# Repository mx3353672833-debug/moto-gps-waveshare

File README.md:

<p>
  
</p>

> **语言 / Language:** 中文 · [English](README.en.md)

# MOTO GPS · Waveshare Edition

[Glimpse 官网](https://maler.top/) · [2026-09-16 近期更新](docs/UPDATES_2026-09-16.md) · [Web 调试入口](https://maler.top/moto-gps/ride.html)

**想自己做一台微雪版？从 [购买、固件烧录与 iPhone 安装教程](docs/WAVESHARE_DIY_GUIDE.md)开始。**

[功能与使用说明书](docs/USER_MANUAL.md) · [真实导航网关配置](docs/GATEWAY_SETUP.md)

**用安卓手机？** 仓库已包含原生 [Android App](platforms/android/README.md)（Kotlin + Compose，与 iOS 共用导航核心和蓝牙协议，不依赖 Google Play 服务），可自行编译安装；真机配对与骑行仍在验证中。继续改进可参考 [用 AI 开发安卓版本](docs/ANDROID_AI_GUIDE.md)。

~~**欢迎一起共创 Glimpse。** 如果你基于这个项目做出了安卓 App，希望你愿意把源码也公开到 GitHub，让其他人能够学习、使用并一起维护。可以先在 [Issues](https://github.com/mx3353672833-debug/moto-gps-waveshare/issues) 聊想做的功能，再通过 Pull Request 贡献代码、修复或文档；请附上构建说明和已测试的机型。我们会保留贡献者署名，相关代码沿用项目现有许可。具体参与方式见 [安卓共创邀请](docs/ANDROID_AI_GUIDE.md#一起开发安卓版本)。~~

当前提供源码自行编译安装；尚无仓库发布的预编译固件、App Store / TestFlight 下载入口。
**iOS 0.3.0（5）已加入发布准备改动，尚未通过 TestFlight 分发。**
教程包含设备选型、原厂备份、Xcode 个人签名、配对、演示与常见问题。

**作者：Maler X · 署名 / 非商业使用 · 实验性样机**

一块装在车把上的圆屏，一个放在包里的 iPhone。手机负责定位、搜索与路线计算，
圆屏通过蓝牙显示简洁导航、速度、相对航向，并遥控 Apple Music。

项目基于 **Waveshare ESP32-S3-Touch-AMOLED-1.75C**，
包含圆屏固件、iOS App、路线网关和网页调试工具。

仓库同时收录自研电路板、V3 外壳、加工审阅资料和完整产品技术方案。
当前运行版本仍是微雪成品板 + iPhone；自研部分按历史工程候选归档，具体版本见下方资料入口。
B1 手机配套主板与 V3 外壳目前暂停推进，现阶段集中完善微雪版本。
首图为产品外观效果图，实物与加工尺寸请以对应版本的工程文件为准。

出发前在手机上搜索目的地、比较路线；开始导航后，车把上的圆屏显示眼前路口、
转向动作和距离。地图围绕固定的车头箭头移动，灰色道路和建筑提供周围环境参照。
滑动屏幕，还可以查看速度、航向，或操作 Apple Music。

[功能详解](#功能详解) · [使用流程](#使用流程) · [硬件与开发环境](#硬件与开发环境) ·
[安装与配置](#安装与配置) · [开发与测试](#开发与测试) · [使用许可](#使用许可与署名)

[产品参数](docs/PRODUCT_SPECIFICATIONS.md) · [电路板与外壳](hardware/README.md) ·
[技术方案 PDF / DOCX](docs/technical-proposal/README.md) · [资料总目录](docs/PROJECT_DOCUMENTATION.md)

## 电路板、外壳与产品资料

| 资料 | 包含内容 | 入口 |
| --- | --- | --- |
| 产品说明与技术参数 | 微雪样机与自研 A1 对照、显示与通信、结构尺寸、数据来源与验证状态 | [产品参数](docs/PRODUCT_SPECIFICATIONS.md) |
| H0175 EVT A1 自研主板 | KiCad 原理图与四层 PCB、项目符号封装库、BOM/CPL、Gerber/钻孔、装配图、ERC/DRC 和 SHA-256 | [A1 完整审阅包](hardware/manufacturing/engineering-candidates/rev-a1-h0175-evt1-20260903/README_DO_NOT_ORDER.md) |
| Rev A0 R4 主板 | A1 之前的路由基线与完整电气审阅资料，保留早期修订供比较 | [R4 审阅包](hardware/manufacturing/engineering-candidates/rev-a0-20260903-r4/README_DO_NOT_ORDER.md) |
| V3 自研外壳 | 参数化 CAD、前框/后壳/卡口 STEP 与 STL、装配模型、二维图、结构规格及外观渲染 | [V3 文件说明](hardware/mechanical/README.md) |
| 产品技术方案 | H0175 EVT A1 与 Rev A0 两版 Markdown、PDF、可编辑 Word，附系统架构与产品配图 | [阅读与下载](docs/technical-proposal/README.md) |
| 审查与生成工具 | 器件封装审计、电气检查、候选包导出脚本及硬件发布检查测试 | [硬件工具](scripts/hardware/README.md) |

自研 A1 使用 Ø52 mm 四层板，历史方案集成 ESP32-S3、LC76G、IMU、磁力计和
充电电源；V3 外壳名义主体 Ø61 × 16 mm，含卡口约 19 mm。这些参数属于自研
设计资料，与当前微雪板的尺寸和器件配置分开列出。A1、R4 均为工程审阅版本，
保留原有 `DO NOT ORDER` 标识；上传资料不代表恢复打样或已完成生产验收。

## 目前有什么

| 模块 | 功能 |
| --- | --- |
| 圆屏导航 | 白色路线、下一动作图标与距离；真实道路限速和红绿灯倒计时尚未接通 |
| iPhone | 原生导航栏与分组列表、浅深色与大字体、位置偏置搜索、搜索历史、路线预览与候选选择 |
| 导航逻辑 | 共享 C++ 核心，路线进度、偏航检测、联网重算与周期路线/路况刷新 |
| 灰色道路 / 建筑 | 默认在线加载周边 OSM / Protomaps 底图；支持城市、区县与沿途下载，保留内置济南地图兜底 |
| 马表 / 航向 | 手机定位提供速度与行驶方向，板载 QMI8658 辅助相对转向 |
| 音乐 | Apple Music 上一首、播放/暂停、下一首 |
| 动效 / 触摸 | 黑白 Logo 淡入淡出、连接状态过渡、滑动切页、指示点自动隐藏、PWR 长按关机 |
| 演示 | 济南大数据产业基地 D 栋附近 → 浪潮总部附近；在线请求与 OSM 离线回退明确区分 |

## 功能详解

### 圆屏导航：把下一个路口看清楚

导航页以黑色为底，白色路线和转向提示是画面的重点。466×466 的圆形显示区域中，
每种元素都有明确含义：

| 画面元素 | 表达的信息 |
| --- | --- |
| 固定车头箭头 | 当前行进位置的视觉锚点，指向屏幕前方 |
| 白色粗线 | 当前导航路线在附近的走向 |
| 灰色细线 | 周围道路的实际几何形状，帮助辨认路口、支路和道路关系 |
| 灰色建筑块 | OSM 中收录的建筑轮廓，提供街区和园区参照 |
| 左下动作图标 | 下一个路口的直行、左转、右转、掉头等动作 |
| 动作旁的大号距离 | 距离这个动作还有多远，按距离切换 `m` / `km` |
| 限速牌 | 已有显示结构，但真实道路限速尚未接通；缺少数据时隐藏 |
| 底部圆弧 | 路线完成进度，颜色随当前路况状态变化 |

例如屏幕显示右转箭头和 `300 m`，意思就是沿当前路线行驶约 300 米后右转。
接近路口时，距离逐渐减少；通过路口后，图标和数字更新为下一项指引。

行驶和转弯时，路线、周边道路和建筑使用同一组位置、航向和缩放参数。
车头箭头保持固定，地图在它下面平移、旋转，便于连续观察前方道路。
圆屏聚焦当前路段，出发前的全程路线由 iPhone 的预览地图展示。

### 地点搜索与路线选择

iPhone App 使用高德地点搜索与普通驾车路线服务。搜索时会带上手机当前位置，
优先呈现附近、相关度较高的地点。在济南输入“奥体中心”这样的关键词即可开始检索，
也可以输入带城市名的外地地点。
当前是普通驾车路线，不保证避开摩托车禁限行道路。

搜索与选路流程包括：

- 输入至少两个字开始搜索，连续输入时合并请求，按最新关键词更新结果。
- 搜索结果显示地点名称、地址或所在区域；有当前位置时可展示距离。
- 选择地点后保存到最近地点列表，按使用顺序保留 **8 条**，重启 App 后继续保留。
- 点击最近地点可重新规划前往该处的路线，也可以一键清空历史。
- 规划前刷新起点位置，再向网关请求候选路线。
- 按高德实际返回结果提供 **最多 3 条路线**，以推荐路线、备选路线展示。

路线确认页会显示起点、终点和整条路线。选中的路线高亮，其余候选以浅色显示。
下方卡片列出各条路线的距离、预计时间和分段路况摘要，例如“路况顺畅”“部分路段缓行”。
点击卡片切换方案，确认后再点击“开始导航”。

开始时会将选中的路线交给导航核心；如果预览后起点已经明显移动，程序会从当前位置
重新规划。路线确认与真机显示的一致性是当前持续回归测试的项目之一。

### 行驶中的导航更新

导航核心根据连续定位更新路线进度、下一动作距离、剩余路程和预计剩余时间。
手机导航页同时显示目的地、圆屏连接状态、定位状态与当前路况。

偏航判断结合偏离距离与连续定位确认。满足条件后，App 发起重新规划，
取得新路线后将指引同步给圆屏。路况通过周期请求刷新；核心默认配置约每 60 秒
发起一次更新，实际请求节奏还受网络状态、重试和服务配额影响。
当前路线仍以白线显示，按路段着色及未知、过期路况的呈现仍在完善。
红绿灯倒计时和可信的当前道路限速数据尚未接通。

定位质量、请求编号、路线版本都参与状态更新。手机保留当前导航状态，
圆屏重新完成连接和协议握手后，程序会尝试补发最新路线与显示数据。
后台连接和跨城路线的验证进展集中记录在[开发进度](#开发进度)。

### 在线周边地图与离线下载

背景小地图使用 OpenStreetMap / Protomaps 道路和建筑数据。配置可用网关后，
导航默认按当前位置在线加载周边底图，保存已访问区域；网络不可用时复用本地数据。
底图已经不限于随包的济南数据，但能否下载及当地道路、建筑完整程度取决于数据源与网络。

在 iPhone 首页进入「地图与离线下载」：

- 「下载城市地图」可搜索城市或区县，预览范围后下载；范围较大时建议先选区县。
- 选好路线后，可「下载这条路线周边」，保存沿途约一公里范围的底图。
- 下载可以暂停、继续和删除；自动缓存最多 128 MB，手动下载最多 512 MB，共用瓦片只保存一份。
- 离线底图不包含实时路况；搜索地点、规划新路线和联网重算仍需要网络。

原有济南 SQLite 地图库仍随 App 提供，作为覆盖区域内的本地兜底：

| 当前内置数据包 | 数量 |
| --- | ---: |
| 文件体积 | 9.73 MiB |
| 道路折线 | 47,468 条 |
| 道路节点 | 266,985 个 |
| 建筑轮廓 | 26,702 个 |
| 建筑节点 | 148,140 个 |

导航时，手机从在线瓦片、已保存地图或可用的济南兜底数据中筛选当前位置周围约 500 米
的道路和建筑，再通过 BLE 发给圆屏。查询窗口随位置滚动，圆屏不保存整座城市地图。

目前单个显示窗口最多容纳 24 条背景道路、192 个道路点，以及 16 个建筑、128 个建筑点。
这种分工让手机保存完整区域数据，圆屏负责绘制当前视野。地图密度取决于当地 OSM
收录情况、要素筛选策略和窗口容量；建筑覆盖较完整的区域会有更丰富的街区细节。

路线规划与路况由在线高德服务提供，圆屏灰色环境图层来自 OSM / Protomaps，
手机全程预览底图由 Apple 地图提供。它们是不同数据层，离线下载不等于离线导航。
长期部署需准备稳定、获准使用的数据源，保留 OSM 署名与许可入口。
新流程见[近期更新](docs/UPDATES_2026-09-16.md)，原有数据库格式和重建工具见
[离线地图说明](shared/offline_map/README.md)。

### 马表与航向页

马表页以大号数字显示当前速度，单位为 `km/h`，外圈刻度和圆弧随速度变化。
页面围绕实时速度设计，适合在圆屏上快速读取。

航向页显示角度、方位字母、旋转刻度和当前速度。手机定位提供行驶方向，
圆屏上的 QMI8658 六轴传感器提供短时角速度，用于补偿转动过程中的显示变化。

手机放在包里时，行驶方向取自位置运动产生的 `CLLocation.course`；
圆屏的相对转角取自设备自身陀螺仪。低速或静止时冻结不可靠的航向变化并抑制残余速度，
恢复行驶后再由定位航向逐渐校正。静止绝对北向属于后续磁力计扩展的范围。

### Apple Music 控制

音乐页通过 iPhone 的系统音乐播放器控制 Apple Music，显示音乐来源、曲目标题、
歌手和播放状态。圆屏提供上一首、播放/暂停、下一首三个操作按钮。

首次使用时，在 iPhone 上授权媒体资料库访问，并在 Apple Music 中准备好播放队列。
触摸圆屏按钮后，命令经 BLE 发送到手机；播放器处理动作后，最新曲目与状态再回传圆屏。
手机授权状态和播放器状态决定音乐功能的可用情况。

声音继续沿用 iPhone 当前的音频输出，例如头盔蓝牙耳机。圆屏承担显示与遥控，
适合与手机现有的音乐播放方式搭配使用。

### 开机、连接与触摸交互

上电后先显示黑白 `MOTO GPS` Logo，经过淡入、停留和淡出进入连接界面。
面板在纯黑首帧准备好后点亮，减少启动闪白。

```text
开机 Logo → 准备连接 / 连接中 → 绿色连接成功 → 准备出发 → 导航画面
```

准备连接时显示连接图形和动画；协议握手完成后，绿色成功状态停留约 0.9 秒，
再进入准备出发页，提示到手机选择目的地。开始规划与取得路线时，页面继续随状态切换。

- 左右滑动切换导航、马表、航向、音乐页面；音乐页按手机能力开放。
- 底部指示点用于识别当前页面，停留五秒后自动隐藏。
- 触摸或换页后，指示点重新出现。
- 侧面 PWR 按住约三秒，显示关机画面并向 AXP2101 请求关机；USB 供电场景还有深睡处理。

### 演示导航

App 提供“演示导航”入口，使用以下公共地点作为固定演示场景：

**济南大数据产业基地 D 栋附近 → 浪潮集团总部附近。**

联网演示优先请求当次高德路线，再沿返回的路线几何连续生成模拟位置。
离线回退使用随仓库提供的 OSM 路线，经过园区车道、新泺大街、崇华路和浪潮路，
全长约 1.49 公里。演示位置同样经过导航核心、BLE 协议和圆屏 UI。

坐在桌前即可观察动作图标与距离的对应关系、地图滚动、转弯旋转、周边灰路与建筑，
也能检查连接状态切换和页面排版。Web 工具提供同源界面的浏览器预览。
演示数据的道路来源、生成方式和 OSM 署名见[演示夹具说明](shared/demo_fixture/README.md)。

## 使用流程

完成首次安装和配置后，一次导航按下面的顺序操作：

1. 给圆屏上电，在 iPhone 上打开 MOTO GPS。
2. 查看连接状态；首次配对时按 iOS 提示完成蓝牙配对和权限授权。
3. 输入目的地，或者从最近地点中选择一个终点。
4. 在全程地图中查看路线，比较候选卡片的距离、用时与路况。
5. 选择路线并点击“开始导航”，手机开始更新位置，圆屏显示当前路段和下一动作。
6. 停车时可滑动查看马表、航向和音乐页面，按需切歌。
7. 到达后查看到达状态，在手机上结束导航；收车时长按圆屏 PWR 关机。

iPhone 提供网络和定位，圆屏通过 BLE 连接手机。当前后台连接可靠性仍在验证中，
请先在安全静止环境完成锁屏、恢复连接和状态同步测试。
调试及操作请停车后进行，行驶时请结合成熟导航软件核对路线。

## 硬件与开发环境

### 终端硬件

| 项目 | 当前适配 |
| --- | --- |
| 开发板 | Waveshare ESP32-S3-Touch-AMOLED-1.75C |
| 主控 | ESP32-S3 |
| 存储 | 32 MB Flash、8 MB PSRAM |
| 显示 | 1.75 英寸圆形 AMOLED，466×466 |
| 显示驱动 | CO5300，QSPI，RGB565 |
| 触摸 | CST9217 电容触摸 |
| 运动传感器 | QMI8658 六轴 IMU |
| 电源管理 | AXP2101，USB-C / 配套锂电池 |
| 手机连接 | BLE，自定义导航 GATT 服务 |

准备一条支持数据传输的 USB-C 线。使用电池时，按微雪对 **1.75C** 的规格、
插头和极性要求选择。刷写前请核对完整板型；板级连接与固件步骤见
[ESP32 说明](platforms/esp32/README.md)。

### 软件工具

| 用途 | 环境 |
| --- | --- |
| iPhone App | iOS 17+；Mac、Xcode 16+ / Swift 6 工具链、XcodeGen |
| 圆屏固件 | ESP-IDF **5.5.5**，Waveshare BSP **3.0.0** |
| 共享 UI | LVGL **9.5.0 对应固定提交** |
| 路线网关 | Node.js 20+；建议 Node.js 24+ 运行本文配置示例 |
| C++ 测试 | CMake、支持 C++17 的编译器 |
| Web 预览 | Emscripten、CMake、HTTP 静态服务器 |
| 地图重建 | Node.js 24+、osmium-tool、jq |

真实导航需要配置自己的高德 Key、HTTPS 网关和 Apple 开发者签名。

## 安装与配置

### 1. 获取源码

```sh
git clone --recurse-submodules https://github.com/mx3353672833-debug/moto-gps-waveshare.git
cd moto-gps-waveshare
```

上述命令会同时获取固定版本的 LVGL。使用 GitHub 的 Download ZIP 时，
还需将 LVGL 提交 `85aa60d18b3d5e5588d7b247abf90198f07c8a63` 的源码放入 `third_party/lvgl/`。

下面的命令均以仓库根目录为起点。

### 2. 配置路线网关

也可以选择新增的 [Cloudflare Workers + R2 部署](backend/cloudflare/README.md)，无需维护 Node 服务器。下面仍是原有服务器方案。

网关将 App 的搜索和路线请求转换为高德 Web 服务请求，再返回统一格式的导航数据。
高德 Key 保存在服务端环境变量中。

先运行后端自动测试，再创建自己的配置文件：

```sh
npm ci --prefix backend
npm --prefix backend test
cp backend/.env.example backend/.env
```

编辑 `backend/.env`：

| 配置项 | 填写内容 |
| --- | --- |
| `MOTO_PROVIDER` | 真实导航填写 `amap`；本地协议测试用 `fixture`；待配置服务用 `disabled` |
| `AMAP_WEB_SERVICE_KEY` | 自己申请的高德 Web 服务 Key |
| `PORT` | 后端监听端口，默认 `8787` |
| `WEB_ORIGIN` | 使用 Web 工具时填写网页的实际 Origin |
| `MOTO_MAP_PMTILES_URL` | `auto` 选择兼容的 Protomaps 构建；也可指定自己的 HTTPS PMTiles 地址，`disabled` 关闭在线底图 |
| `MOTO_MAP_CACHE_DIR` | 地图缓存目录，默认 `.cache/map-tiles` |
| `MOTO_MAP_CACHE_MAX_BYTES` | 服务端缓存字节上限，默认 `1073741824` |

用 Node.js 24+ 显式加载配置并启动：

```sh
node --env-file=backend/.env backend/src/server.js
```

服务默认监听 `127.0.0.1:8787`。部署时，用自己的 HTTPS 反向代理把
`/moto-gps/api/` 转发到这个服务，供手机访问。
检查 `/healthz` 中的 `provider` 为 `amap`、`ready_for_live_navigation` 为 `true`，
再完成一次真实地点搜索与路线请求，确认账号权限、配额和网络。

对公网部署时，请配置访问控制、TLS、配额限制和日志脱敏。
完整 API 与部署说明见[路线网关文档](backend/README.md)。

### 3. 构建并安装 iPhone App

也可以直接下载 IPA，在 App 中填写网关地址，无需自己用 Mac 编译：[IPA 安装说明](docs/IOS_SIDELOAD.md)。

编辑 `platforms/ios/project.yml`，设置：

- `MOTOGPSGatewayBaseURL`：自己的 HTTPS 网关地址，例如 `https://YOUR-DOMAIN/moto-gps/api/`。
- `PRODUCT_BUNDLE_IDENTIFIER`：自己可用的唯一标识；App 与两个测试目标分别设置。
- `DEVELOPMENT_TEAM`：自己的签名团队，也可以在 Xcode 中选择。

App 默认网关为示例地址 `https://example.invalid/moto-gps/api/`，使用前替换成自己的服务。
配置来源是 `project.yml`，XcodeGen 会据此更新工程与 `Info.plist`。

```sh
(cd platforms/ios && xcodegen generate)
open platforms/ios/MotoGPS.xcodeproj
```

连接并信任自己的 iPhone，按 Xcode 提示启用开发者模式，选择 MotoGPS scheme、
自己的设备和签名团队，再点击 Run 安装。
首次运行按提示允许定位、精确位置、蓝牙及所需媒体权限。
详细步骤和签名说明见[iOS 文档](platforms/ios/README.md)。

### 4. 构建并刷入圆屏

安装、激活 ESP-IDF 5.5.5 环境后执行：

```sh
idf.py -C platforms/esp32 set-target esp32s3
idf.py -C platforms/esp32 build
```

构建会获取固定依赖，在 `platforms/esp32/build/` 生成应用、bootloader 和分区表。
首次刷写前，按[固件文档的备份步骤](platforms/esp32/README.md#备份和刷写)
核对型号、Flash 容量和安全状态，保存原厂完整备份。

确认备份完成并接受替换原厂应用后，将 `PORT` 换成实际 USB 串口：

```sh
idf.py -C platforms/esp32 -p PORT flash monitor
```

设备启动后以 `MOTO GPS` 广播。打开 iPhone App 完成配对与握手，
圆屏进入准备出发页后，即可按照上面的使用流程选择路线。

### 5. 在浏览器预览界面

安装并激活 Emscripten 后，构建共享 LVGL WebAssembly 运行时：

```sh
./scripts/build_web.sh
python3 -m http.server 4173 --directory .
```

浏览器打开：

```text
http://127.0.0.1:4173/platforms/web/shell/index.html?demo=1
```

也可以分别预览连接状态，把查询参数改为 `?deviceState=connecting`、
`?deviceState=success`、`?deviceState=ready` 或 `?deviceState=planning`。
这些状态使用共享 LVGL 界面渲染，适合开发时检查动画和排版。

查看和调试界面可用 [Web 调试工具](platforms/web/shell/README.md)，使用时保持网页前台亮屏。
线上调试入口是 [/moto-gps/ride.html](https://maler.top/moto-gps/ride.html)；
[Glimpse 官网](https://maler.top/) 位于域名首页，网站本身不开源。
手机后台定位和 BLE 连接由 iOS App 负责，当前验证进度见[已知问题](docs/KNOWN_ISSUES.md)。

## 实现方式

iPhone 负责位置、完整路线、地图下载与缓存，ESP32 负责接收显示状态、处理本机运动输入、
绘制圆屏和回传触摸命令。后端负责高德服务调用、Protomaps 数据读取、格式转换与缓存。

```text
高德 Web 服务 ───────┐
OSM / Protomaps ─────┴→ HTTPS 网关与缓存 ←→ iPhone App
                                      │
                Core Location + 共享导航核心 + 在线 / 离线地图查询
                                      │ BLE
                                      ▼
                   ESP32 接收状态 + QMI8658 相对转向
                                      │
                           NavPresenter → LVGL → 圆屏

圆屏触摸 / 音乐操作 ─────── BLE ───────→ iPhone
```

### 共享导航与界面

路线进度、偏航状态和显示数据结构放在共享 C++ 模块中。iOS 通过 Objective-C++ 桥接调用
导航核心；Web 和 ESP32 共同编译 `NavPresenter` 与 LVGL UI。
调整圆屏布局、动作图标或地图绘制时，可以先用 Web 观察，再在实机验证。

完整路线保存在手机端，圆屏接收当前视野所需的路线几何与周边环境窗口。
请求位置使用 WGS84，导航几何统一为 GCJ-02；地图预览按平台坐标要求进行转换。
相关约定见[架构说明](docs/ARCHITECTURE.md)和[路线协议](shared/protocol/README.md)。

### BLE 数据与连接

设备以 GATT peripheral 工作，iPhone 作为 central 连接。
协议包含连接状态、心跳、导航快照、路线几何、路况、道路/建筑窗口、媒体状态和设备命令。

传输层实现分片重组、CRC 校验、消息序号、会话隔离、控制命令 ACK 与超时重试。
手机到圆屏的导航快照最高按 5 Hz 调度，位置和转向动画由终端进一步插值。
配对采用加密 BLE 连接与 bonding；连接恢复仍在持续测试。
心跳只发送当前应用会话的已用时间，不发送手机系统启动时长。
GATT UUID、字节格式与黄金测试数据见[BLE 协议](shared/protocol/ble-navigation-v1.md)。

### 显示与流畅度

固件使用 PSRAM 绘图缓冲与直接 DMA，让 LVGL 绘制和 QSPI 传输衔接。
CO5300 的 TE 信号用于帧首同步，地图、插值和渲染任务按 25 ms 的目标节拍协调。
实际帧率、快速转向时的撕裂感和持续运行功耗，仍以实机测量与观察为准。

## 源码结构

```text
platforms/ios       iPhone 定位、路线预览、BLE、Apple Music、在线 / 离线地图
backend            Node.js 高德服务与 Protomaps 地图网关、缓存（Key 只在服务端）
platforms/esp32     Waveshare 板级适配、BLE、QMI8658、显示与电源
shared             共享导航核心、协议、LVGL UI、OSM 演示及地图数据
platforms/web      LVGL / Wasm 调试外壳
website            Glimpse 官网源码与部署说明
tests              C++ 原生测试
scripts            Web 构建、字体与 OSM 地图工具
```

详见 [架构与数据边界](docs/ARCHITECTURE.md)、[测试方式](docs/TESTING.md)、
[已知问题](docs/KNOWN_ISSUES.md)、[第三方许可证](THIRD_PARTY_NOTICES.md)。

## 开发与测试

### 运行自动测试

在仓库根目录执行：

```sh
cmake -S . -B build/native -DMOTO_BUILD_WEB=OFF -DMOTO_BUILD_TESTS=ON
cmake --build build/native --parallel 4
ctest --test-dir build/native --output-on-failure

npm ci --prefix backend
npm --prefix backend test
swift test --package-path platforms/ios

node scripts/generate_jinan_demo_fixture.mjs --check
node scripts/offline_map/validate_jinan_sqlite.mjs
```

2026-09-16 本轮通过 9 组 C++ 原生测试、60 项后端测试、12 项 Swift 核心测试，
并有 13 项 BLE 策略测试通过记录；演示夹具一致性与地图数据库完整性检查通过。
这些结果验证代码和数据路径，不代表真实道路、长时间锁屏或续航验收完成。
本轮范围见[近期更新](docs/UPDATES_2026-09-16.md)；首次公开快照的历史结果保留在
[发布检查记录](docs/RELEASE_CHECKS.md)，提交后的检查结果见
[GitHub Actions](https://github.com/mx3353672833-debug/moto-gps-waveshare/actions/workflows/checks.yml)。

### 从哪里开始修改

| 想调整的内容 | 主要入口 |
| --- | --- |
| 圆屏布局、颜色、图标、状态动画 | `shared/nav_ui/src/moto_nav_ui.cpp` |
| 地图投影与显示数据转换 | `shared/nav_presenter/src/moto_nav_presenter.cpp` |
| 偏航、到达、定位有效期和路况刷新默认配置 | `shared/nav_core/nav_core.hpp` 中的 `NavCoreConfig` |
| 手机搜索、历史记录、路线确认流程 | `platforms/ios/App/AppModel.swift`、`ContentView.swift` |
| 全程路线地图与候选展示 | `platforms/ios/App/RouteOverviewMap.swift` |
| BLE 握手、发送调度与恢复连接 | iOS 的 `ESP32BLECentral.swift` 与 ESP32 的 `ble_nav_transport_nimble.cpp` |
| 当前窗口道路与建筑筛选 | `platforms/ios/App/Adapters/OfflineMap/` |
| Apple Music 遥控 | `platforms/ios/App/Adapters/Media/AppleMusicRemoteController.swift` |
| CO5300 显示、TE 同步与电源 | `platforms/esp32/main/board_port_waveshare_1_75c.cpp` |
| 地图数据重建 | `scripts/offline_map/` |

修改协议时请同步更新两端实现和 golden fixture；修改地图时保留 OSM 来源、许可和署名。
贡献流程见[CONTRIBUTING](CONTRIBUTING.md)。

## 开发进度

当前版本处于实机验证阶段，接下来重点回归：

- iPhone 锁屏、切换网络和离开原环境后的 BLE 连接恢复。
- 跨城候选路线生成，以及手机选中路线与圆屏显示的一致性。
- 在线与离线地图切换、下载中断恢复，以及路况分段显示和过期状态。
- 快速转向时的刷新连续性、TE 同步表现和持续帧率。
- USB、电池及组合供电下的关机、唤醒、续航和温升。

功能说明描述的是当前源码实现；最新发布与验证边界见[近期更新](docs/UPDATES_2026-09-16.md)，
历史问题见[已知问题](docs/KNOWN_ISSUES.md)。提交问题时请附上板型、固件版本、iOS 版本、
复现步骤与脱敏日志，便于区分定位、网关、协议和显示环节。

## 使用许可与署名

项目原创代码和设计素材使用 **[PolyForm Noncommercial 1.0.0](LICENSE.md)**。
允许许可范围内的个人学习、研究、非商业使用和修改；分发源码、修改版、固件或 App
时必须携带许可证及 [NOTICE](NOTICE) 中的作者声明，注明 **Maler X** 和本仓库来源。
App 待机界面和 Web 状态页也提供可见署名入口。

**仅限非商业使用。** 销售预装设备、收费分发固件、用于商业产品或收费服务等用途，
须另行联系作者取得商业授权。具体授权范围以 LICENSE.md 正文为准。

授权类型为 **source-available（公开源码、非商业授权）**。
第三方库、字体和 OSM 数据分别遵循原许可证；地图服务须按服务商协议使用。

© 2026 Maler X · 地图数据 © OpenStreetMap contributors（ODbL 1.0）。

## Star History

<a href="https://star-history.com/#mx3353672833-debug/moto-gps-waveshare&Date">
 <picture>
   <source media="(prefers-color-scheme: dark)" srcset="https://api.star-history.com/svg?repos=mx3353672833-debug/moto-gps-waveshare&type=Date&theme=dark" />
   <source media="(prefers-color-scheme: light)" srcset="https://api.star-history.com/svg?repos=mx3353672833-debug/moto-gps-waveshare&type=Date" />
   
 </picture>
</a>

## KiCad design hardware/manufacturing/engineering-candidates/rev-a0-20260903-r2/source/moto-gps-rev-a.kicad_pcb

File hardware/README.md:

> **语言 / Language:** 中文 · [English](README.en.md)

# MOTO GPS 自研电路板与外壳

这里保存已完成的主板设计、制造审阅文件、外壳模型和核验记录。当前软件样机使用微雪成品板；
自研主板与外壳处于归档/暂停状态。完整资料公开供阅读、研究和工程评审。

## 从哪里开始

| 目标 | 推荐文件 | 说明 |
| --- | --- | --- |
| 查看产品参数 | [参数对照](../docs/PRODUCT_SPECIFICATIONS.md) | 微雪样机与自研 A1 分开列出 |
| 打开最新自研 PCB | [A1 KiCad 工程](manufacturing/engineering-candidates/rev-a1-h0175-evt1-20260903/source/moto-gps-rev-a1.kicad_pro) | 下载整个 source 目录，保留符号与封装库 |
| 阅读 A1 电气状态 | [A1 状态单](rev_a/H0175_EVT_A1_STATUS.md) | 器件、接口、ERC/DRC 与待验证项 |
| 查看 BOM、CPL 和装配图 | [A1 documents](manufacturing/engineering-candidates/rev-a1-h0175-evt1-20260903/documents/) | 原理图 PDF、装配 PDF、器件清单与坐标 |
| 查看 Gerber / 钻孔 | [A1 审阅制造文件](manufacturing/engineering-candidates/rev-a1-h0175-evt1-20260903/review_gerbers_DO_NOT_ORDER/) | 保留工程审阅标记，尚未生产放行 |
| 对照前一版 PCB | [Rev A0 R4](manufacturing/engineering-candidates/rev-a0-20260903-r4/) | A1 的冻结路由基线 |
| 编辑/打印外壳原型 | [V3 STEP 与 STL](mechanical/generated/v3/) | 含前框、后壳、佳明卡口与装配模型 |
| 核对机械尺寸 | [V3 机械规格](mechanical/V3_MECHANICAL_SPEC.md)、[二维图](mechanical/drawings/) | 主体 Ø61 × 16 mm，含卡口约 19 mm，均为设计值 |
| 阅读完整方案 | [技术方案 PDF / Word](../docs/technical-proposal/README.md) | A1 与 A0 两版完整资料 |

A1 与 R4 的完整候选包都包含 `SHA256SUMS`，可在各候选包目录运行
`shasum -a 256 -c SHA256SUMS` 校验。封装、线路和规则检查记录随包提供。
优先使用这些完整候选包；下面保留的 `pcb/` 目录属于更早期的板框研究。

## 早期目录与设计记录

本目录承载 MOTO GPS 自研一体主板、制造文件和外壳 CAD。设计基线见 [自研一体硬件与外壳执行方案](../docs/CUSTOM_HARDWARE_PLAN.md)。

计划结构：

```text
hardware/
  pcb/
    moto-gps-rev-a.kicad_pro
    moto-gps-rev-a.kicad_sch
    moto-gps-rev-a.kicad_pcb
  libraries/       经复核的自建符号、封装与 3D 模型
  mechanical/      参数化外壳、STEP、STL 与 2D 加工图
  manufacturing/   Gerber、钻孔、BOM、CPL 和装配说明
  validation/      上电、RF、GNSS、罗盘、功耗和环境测试记录
```

在屏幕 FPC、电池、GNSS 天线和车把卡口四项冻结前，`manufacturing/` 中的任何文件都只能标为草案，不能直接批量下单。

CAD 工具链为 KiCad 10.0.6。`pcb/` 下的早期文件是 52 mm 圆板机械包络和空白原理图骨架。
后续 `rev_a/` 与制造候选包已经包含真实布线和完整电气设计；两类文件的零违规报告含义不同，
查看时请同时核对版本和工程内容。

已冻结/待冻结的关键接口：

- [屏幕与触摸 FPC 接口](pcb/DISPLAY_INTERFACE.md)：电气映射已整理，连接器接触面、Pin 1 与 FPC 厚度仍须用原装屏实物确认。
- [LC76G 与 GNSS RF 接口](pcb/GNSS_INTERFACE.md)：裸模组、低噪声供电、UART/PPS、U.FL 有源天线基线和塑料 RF 窗约束。
- [电源架构冻结条件](pcb/POWER_DECISION.md)：主方案已改为 BQ25628E + TPS63070 + TUSB320LAI，完整主板前须先通过独立电源测试券。
- [Rev A GPIO 预算](pcb/REV_A_PIN_BUDGET.md)。
- [Rev A0 参数化外壳](mechanical/README.md)：铝前框、塑料后壳、独立 RF 舱和可替换车把卡口概念件。

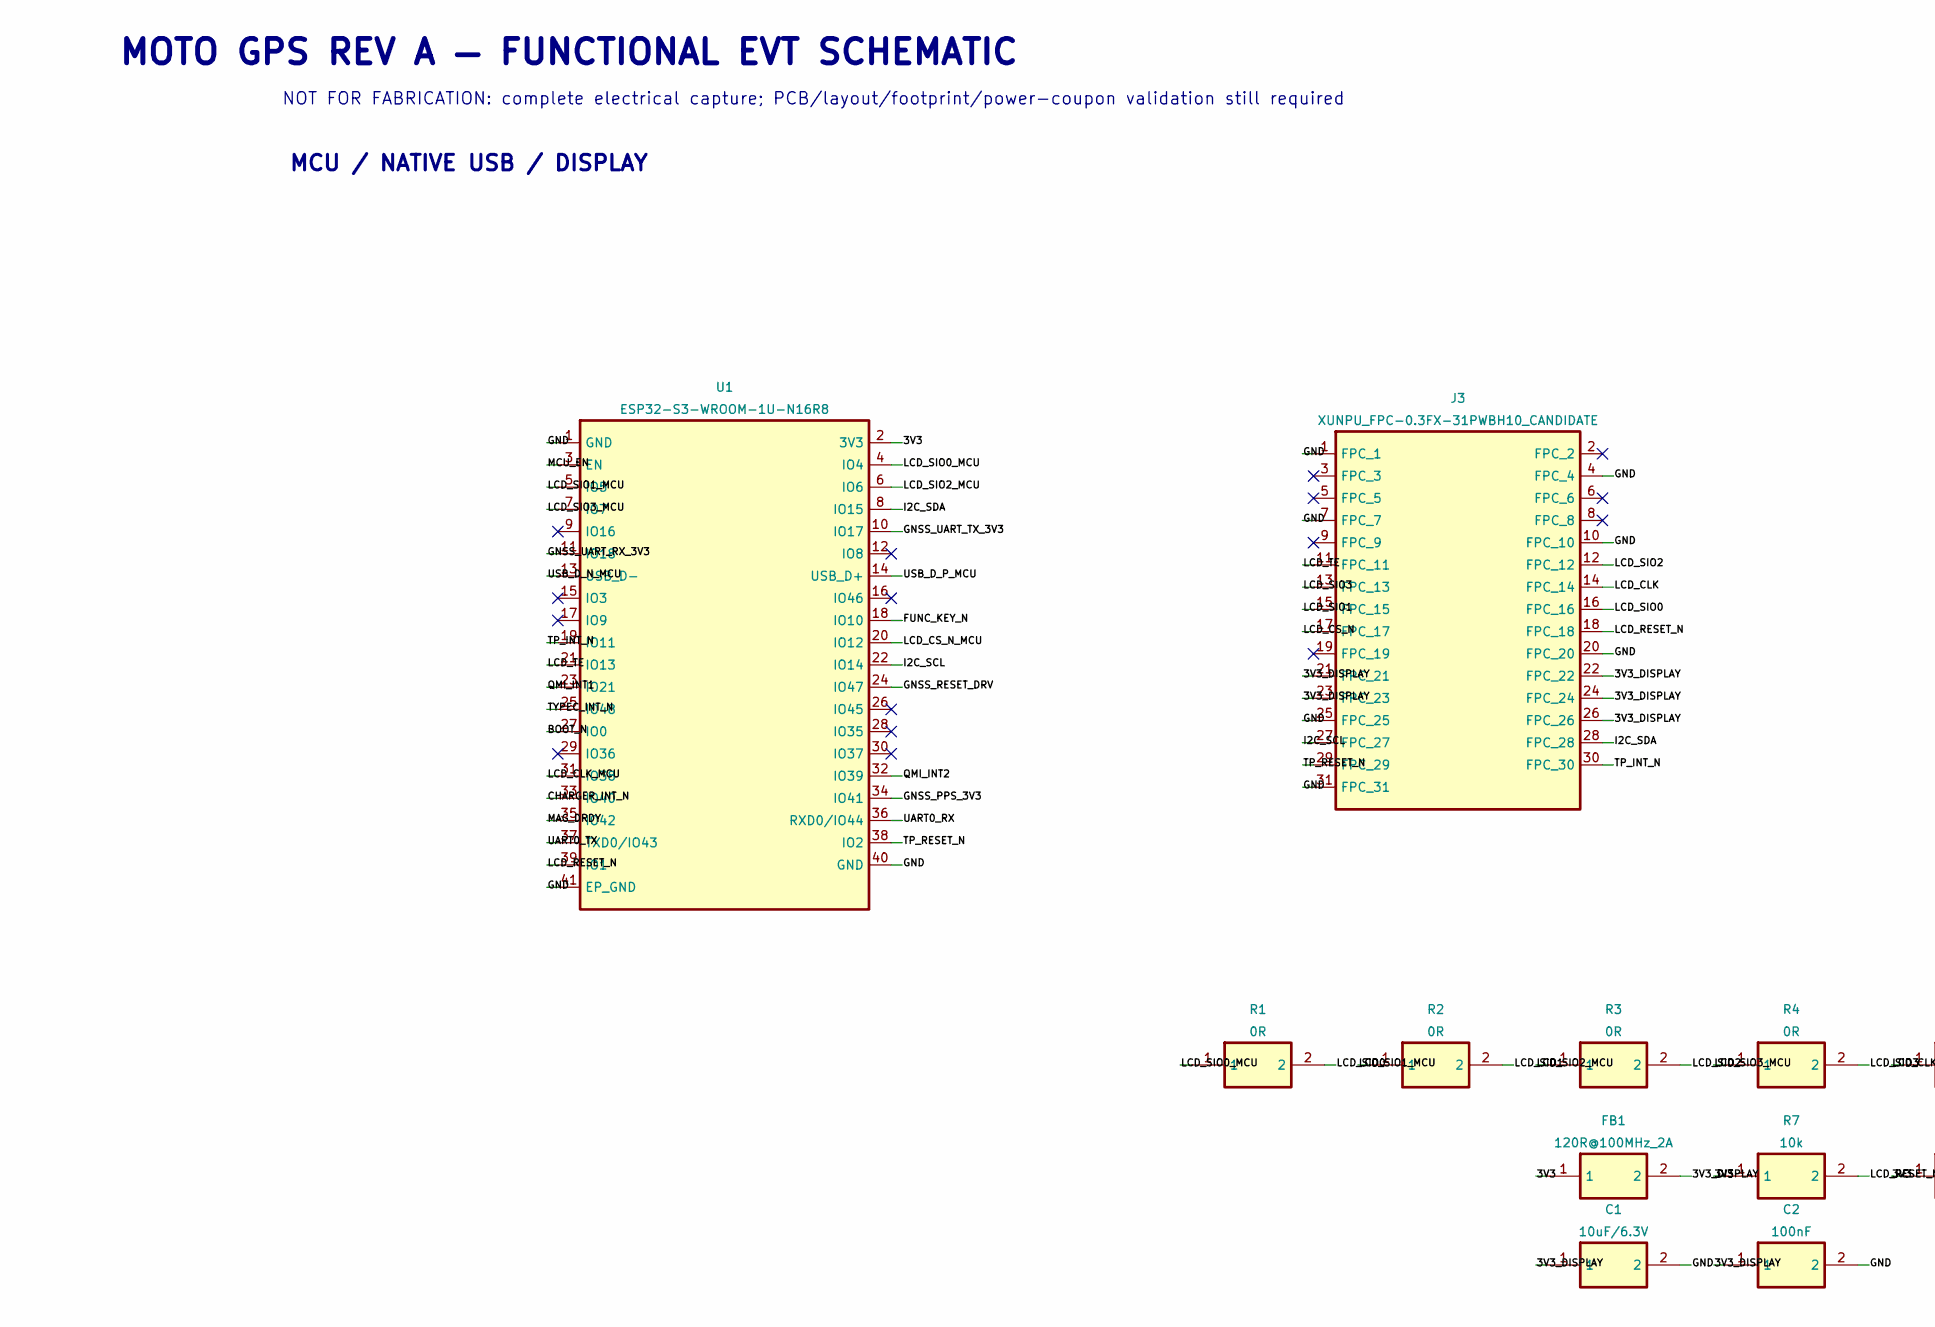
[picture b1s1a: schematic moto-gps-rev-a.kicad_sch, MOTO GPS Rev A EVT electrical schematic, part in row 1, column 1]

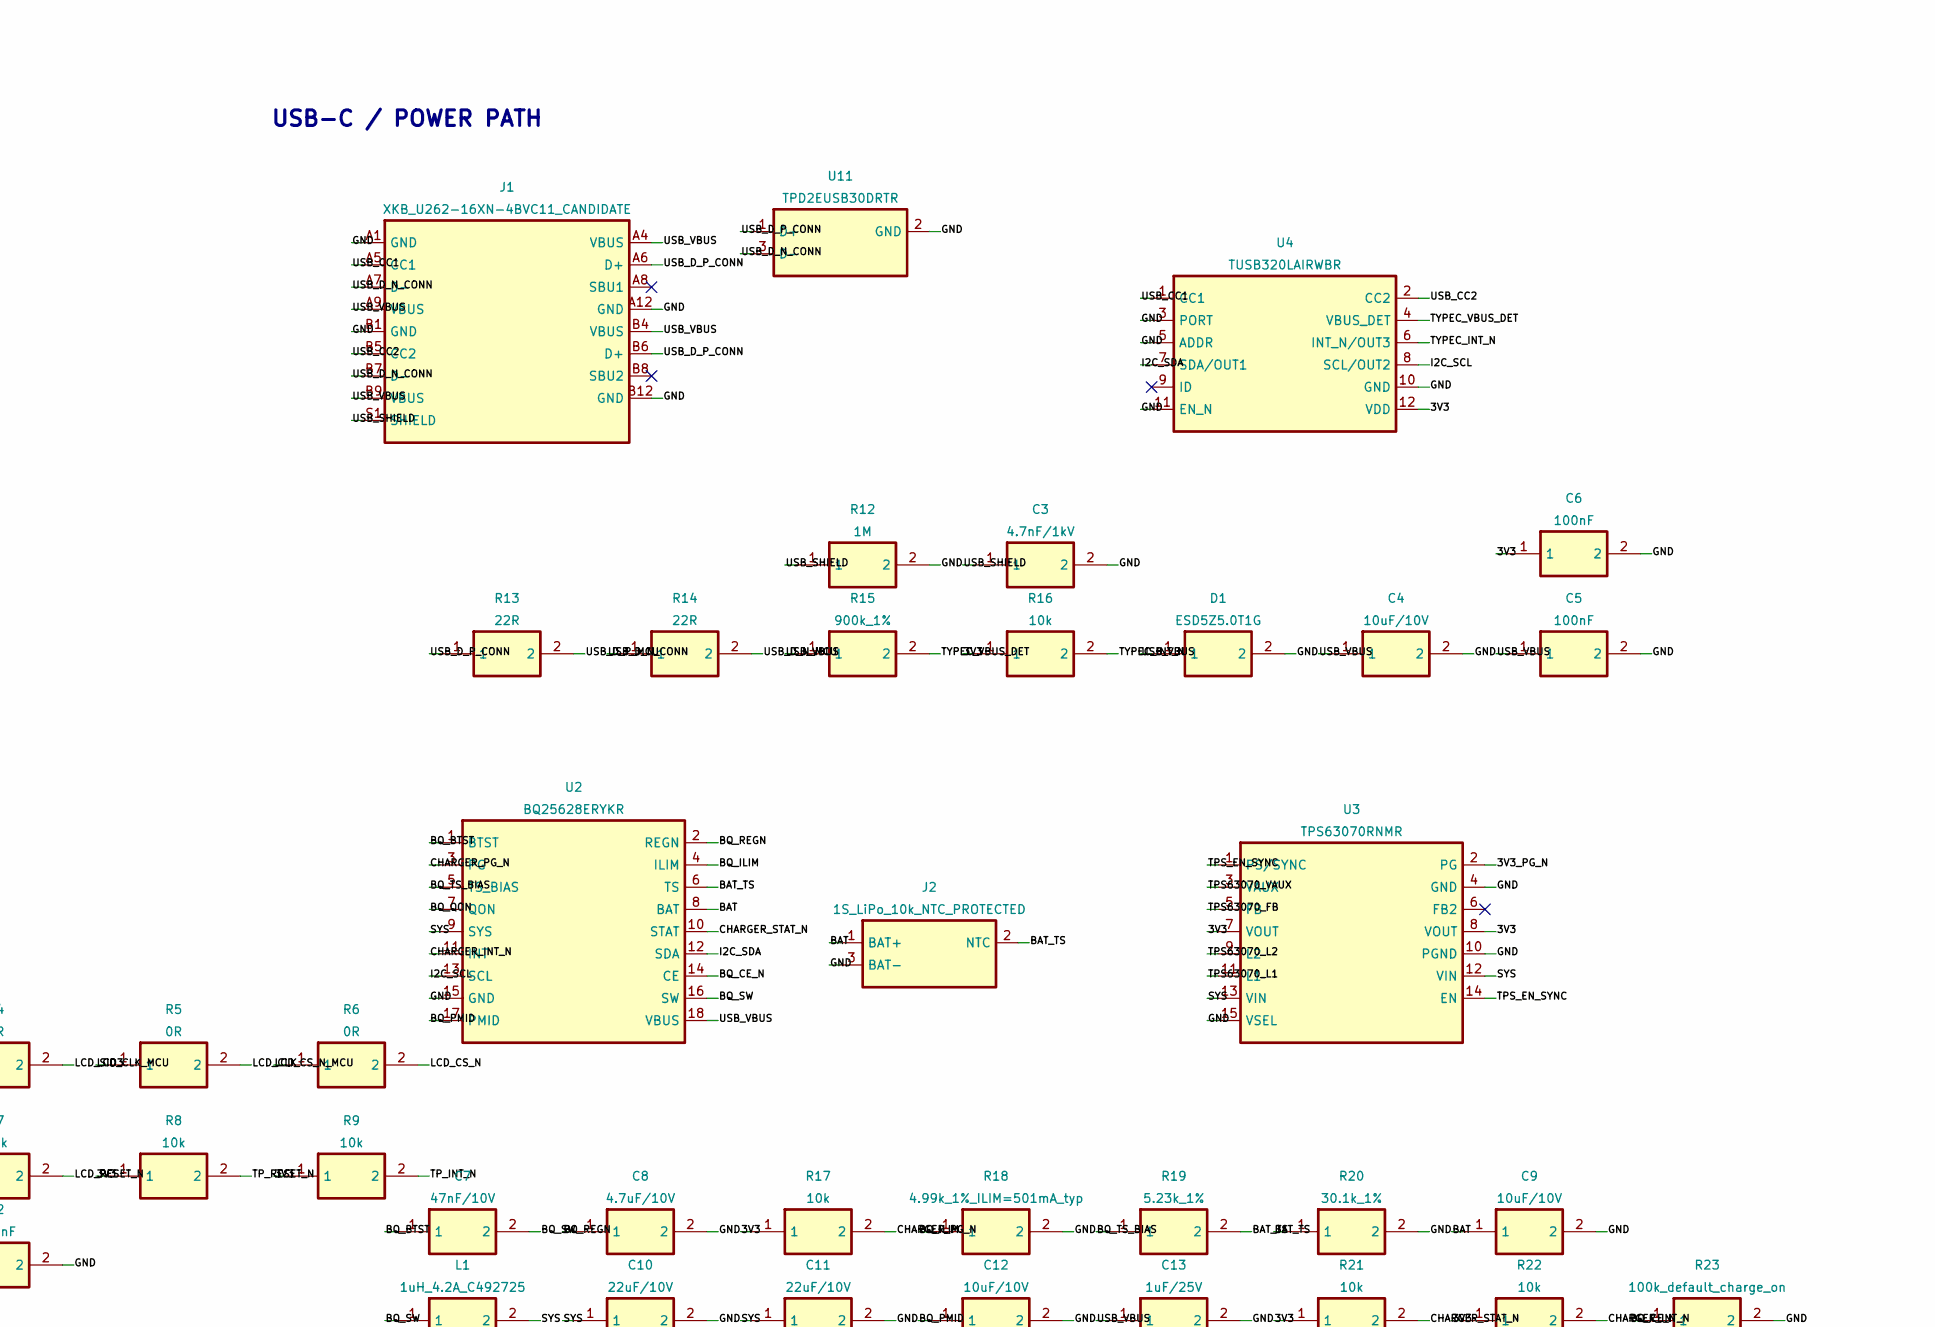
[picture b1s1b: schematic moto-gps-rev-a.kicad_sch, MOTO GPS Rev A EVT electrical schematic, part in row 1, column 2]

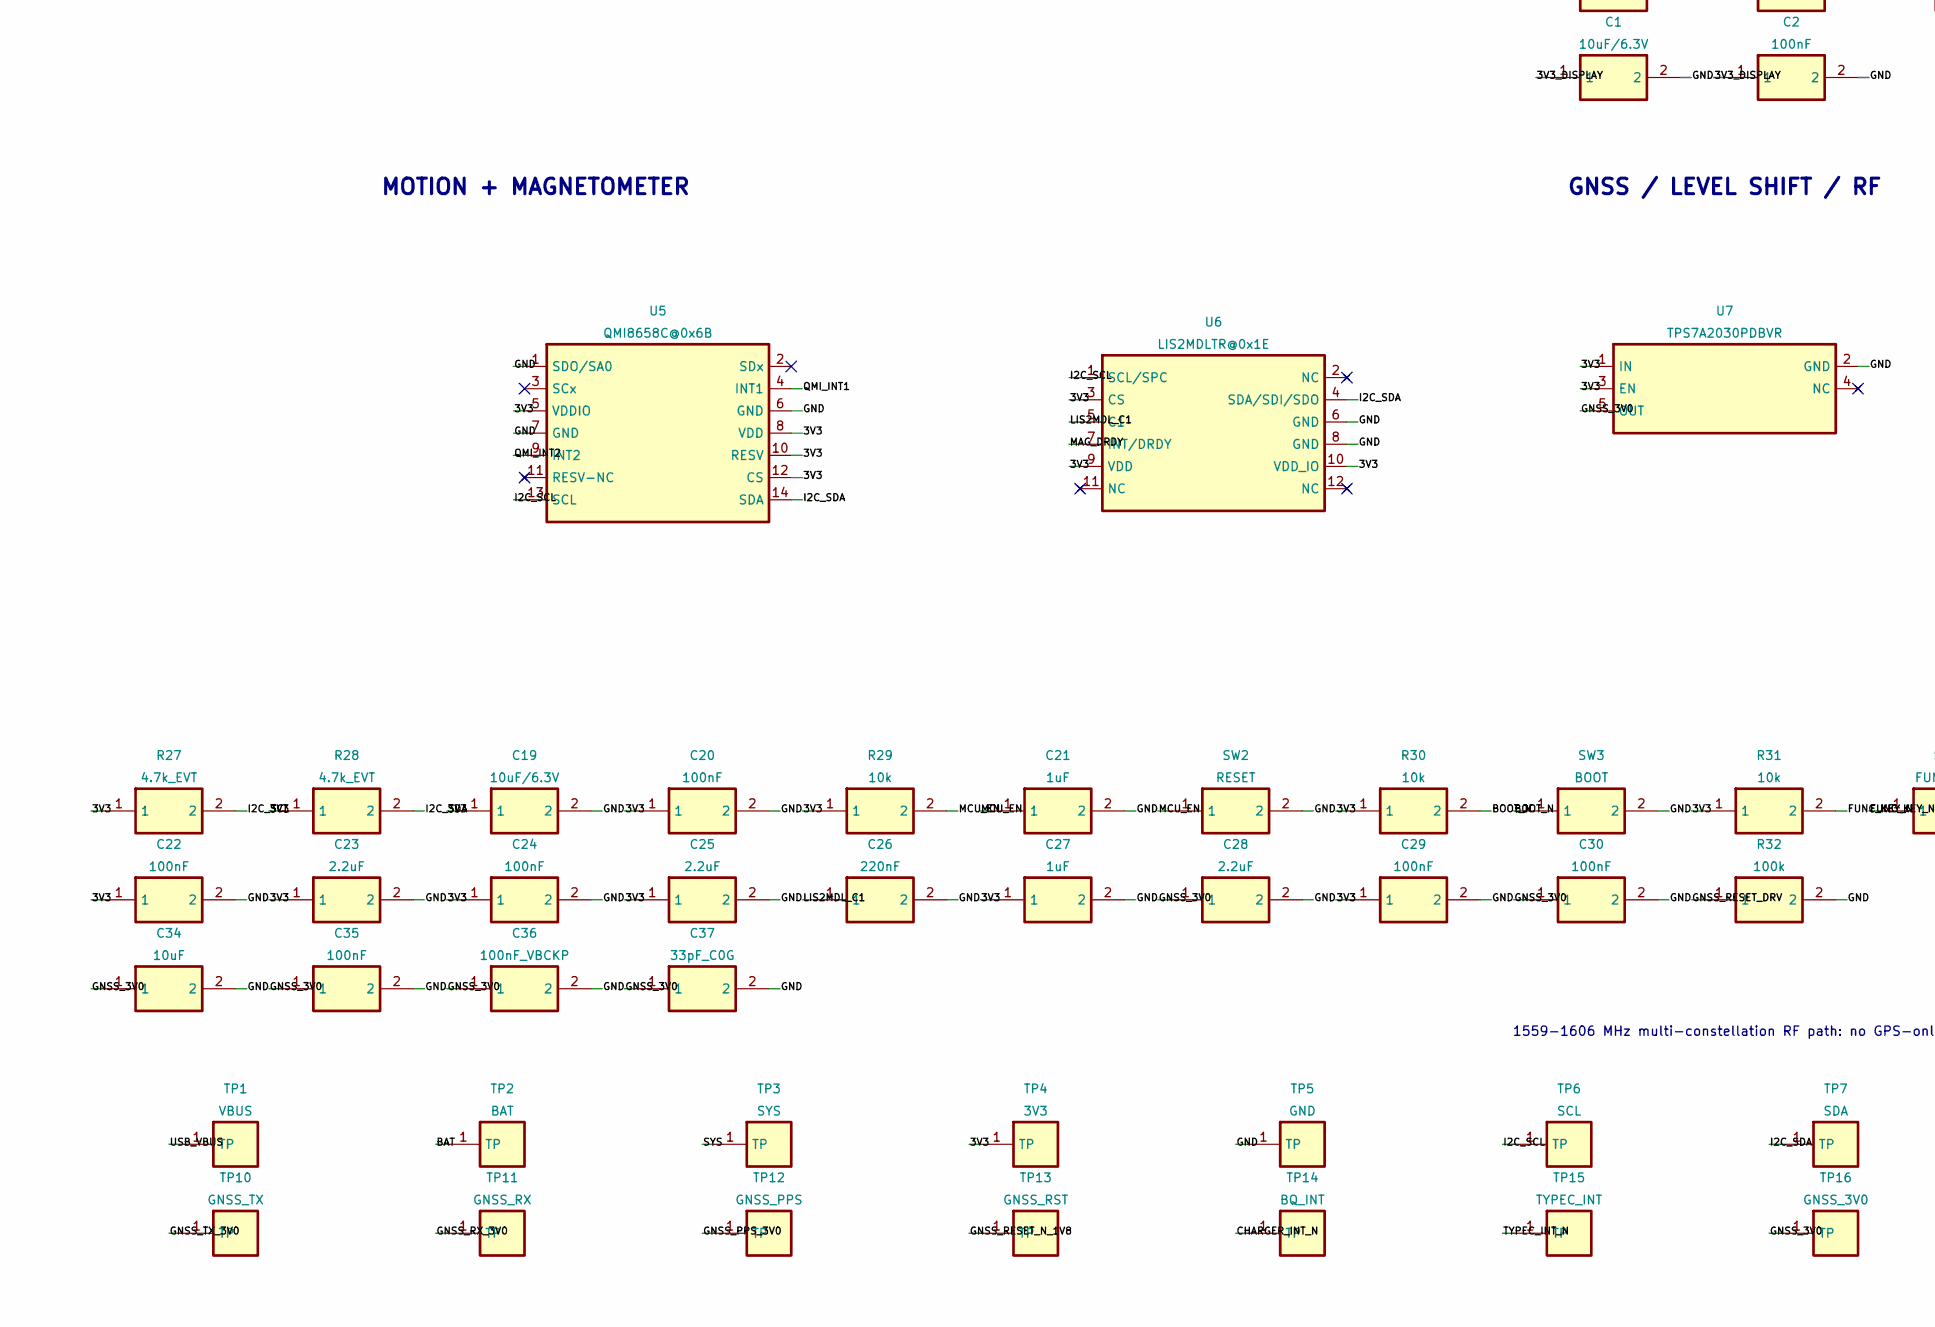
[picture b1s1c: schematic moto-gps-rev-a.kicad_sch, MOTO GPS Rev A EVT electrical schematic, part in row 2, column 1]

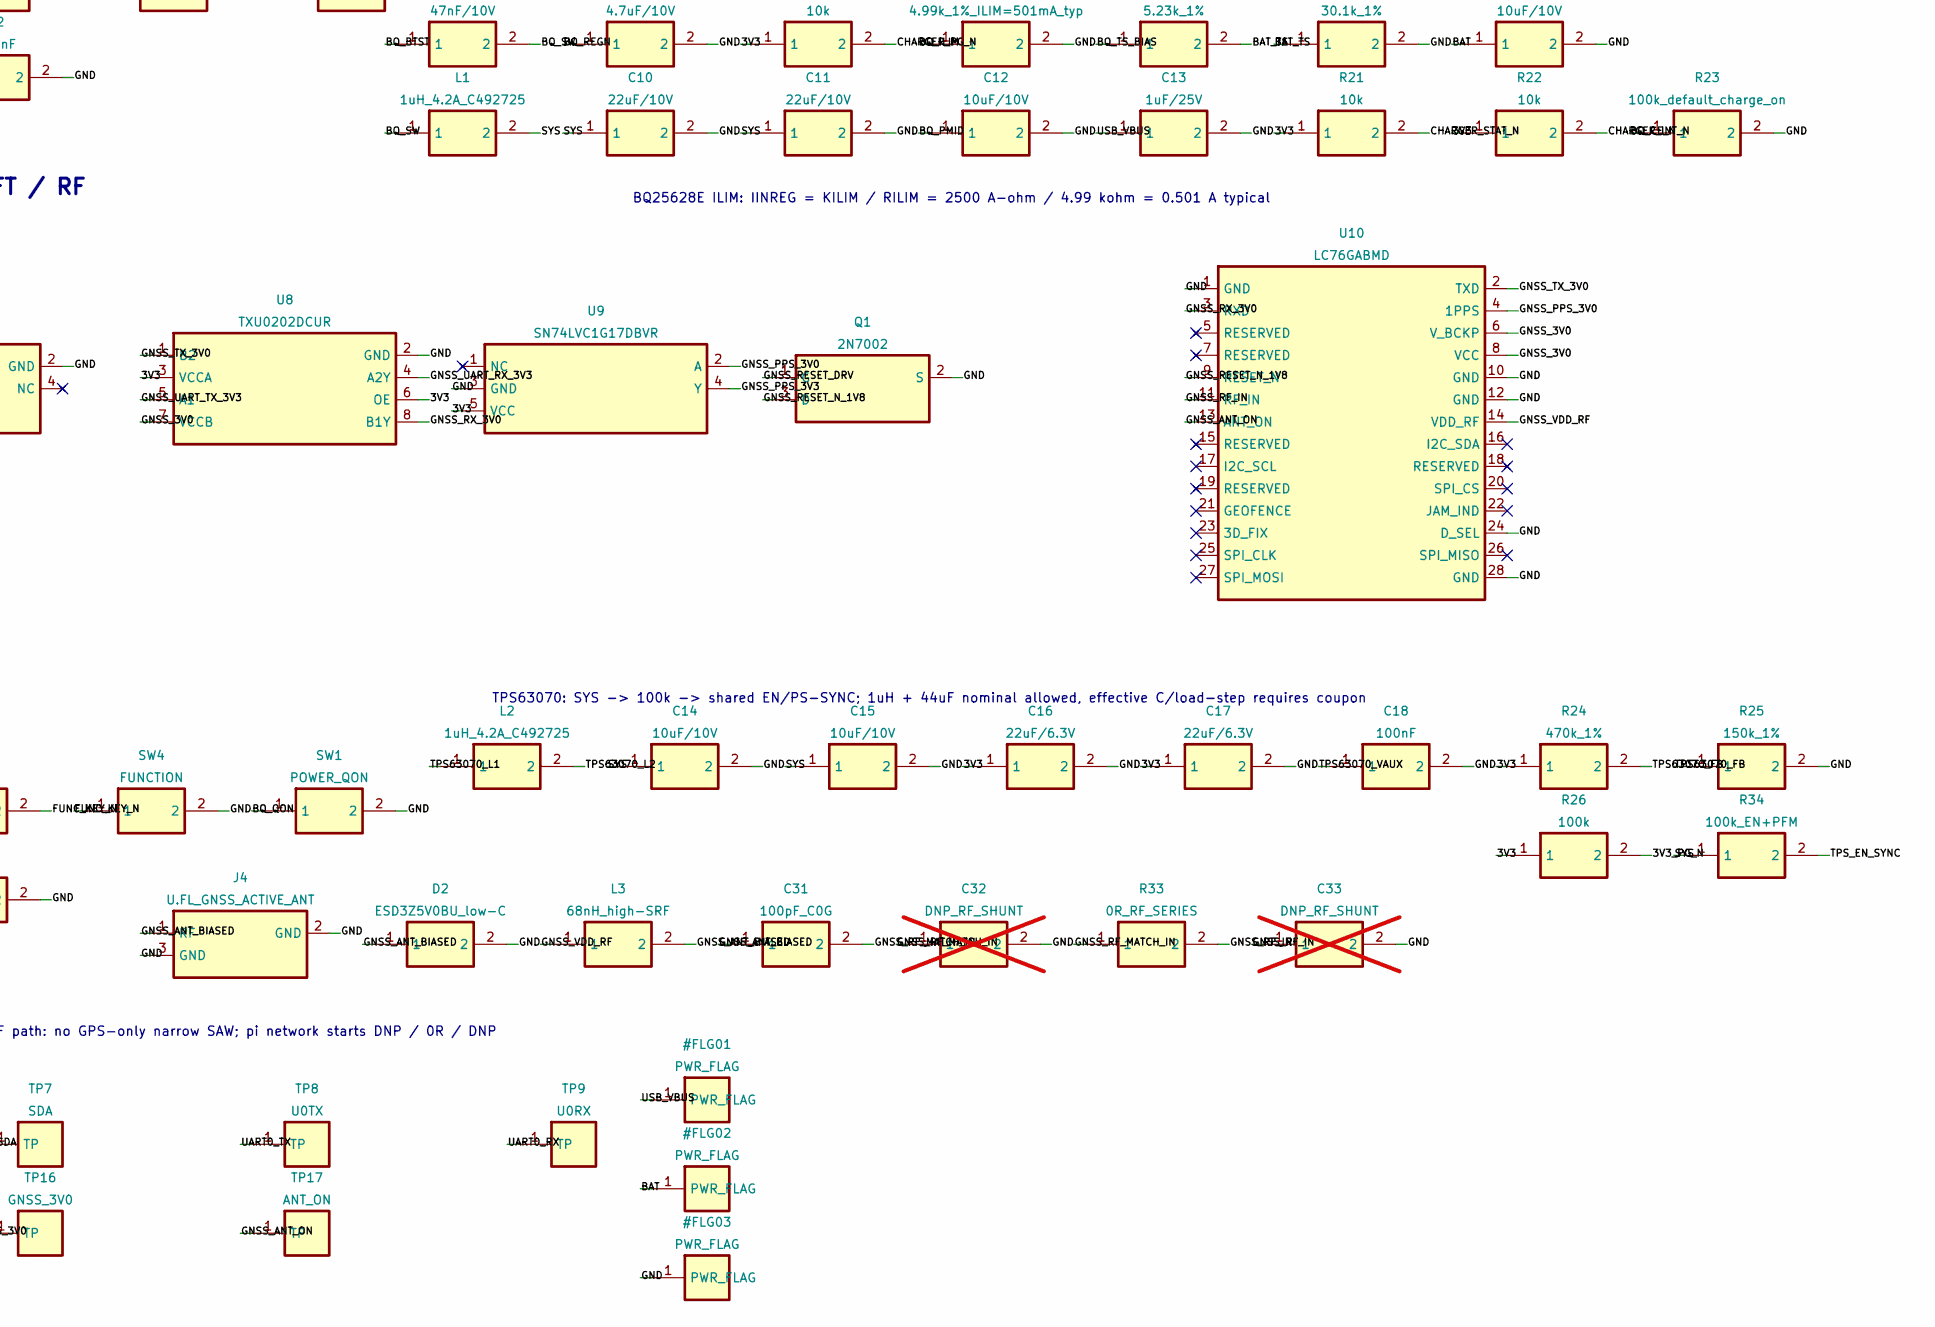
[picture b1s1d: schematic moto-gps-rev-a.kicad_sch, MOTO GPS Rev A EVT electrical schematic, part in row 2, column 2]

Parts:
C1, C19: 10uF/6.3V; C_0603_1608Metric
C2, C5, C6, C18, C20, C22, C24, C29, C30, C35: 100nF; C_0402_1005Metric
C3: 4.7nF/1kV; C_0603_1608Metric
C4, C9, C12: 10uF/10V; C_0603_1608Metric
C7: 47nF/10V; C_0402_1005Metric
C8: 4.7uF/10V; C_0603_1608Metric
C10, C11: 22uF/10V; C_0805_2012Metric
C13: 1uF/25V; C_0603_1608Metric
C14, C15: 10uF/10V; C_0805_2012Metric
C16, C17: 22uF/6.3V; C_0805_2012Metric
C21, C27: 1uF; C_0402_1005Metric
C23, C25, C28: 2.2uF; C_0603_1608Metric
C26: 220nF; C_0402_1005Metric
C31: 100pF_C0G; C_0402_1005Metric
C32, C33: DNP_RF_SHUNT; C_0402_1005Metric; not fitted
C34: 10uF; C_0603_1608Metric
C36: 100nF_VBCKP; C_0402_1005Metric
C37: 33pF_C0G; C_0402_1005Metric
D1: ESD5Z5.0T1G; D_SOD-523
D2: ESD3Z5V0BU_low-C; D_SOD-882
FB1: 120R@100MHz_2A; L_0603_1608Metric
J1: XKB_U262-16XN-4BVC11_CANDIDATE; USB_C_XKB_U262-16XN-4BVC11_MOTO_REVA
J2: 1S_LiPo_10k_NTC_PROTECTED; JST_SH_SM03B-SRSS-TB_MOTO_REVA
J3: XUNPU_FPC-0.3FX-31PWBH10_CANDIDATE; XUNPU_FPC-0.3FX-31PWBH10
J4: U.FL_GNSS_ACTIVE_ANT; UFL_Hirose_UFL-R-SMT-1_MOTO_REVA
L1, L2: 1uH_4.2A_C492725; L_Changjiang_FTC252012S
L3: 68nH_high-SRF; L_0402_1005Metric
Q1: 2N7002; SOT-23
R1, R2, R3, R4, R5, R6: 0R; R_0402_1005Metric
R7, R8, R9, R16, R17, R21, R22, R29, R30, R31: 10k; R_0402_1005Metric
R12: 1M; R_0402_1005Metric
R13, R14: 22R; R_0402_1005Metric
R15: 900k_1%; R_0402_1005Metric
R18: 4.99k_1%_ILIM=501mA_typ; R_0402_1005Metric
R19: 5.23k_1%; R_0402_1005Metric
R20: 30.1k_1%; R_0402_1005Metric
R23: 100k_default_charge_on; R_0402_1005Metric
R24: 470k_1%; R_0402_1005Metric
R25: 150k_1%; R_0402_1005Metric
R26, R32: 100k; R_0402_1005Metric
R27, R28: 4.7k_EVT; R_0402_1005Metric
R33: 0R_RF_SERIES; R_0402_1005Metric
R34: 100k_EN+PFM; R_0402_1005Metric
SW1: POWER_QON; SW_SPST_EVQP7C
SW2: RESET; SW_SPST_EVQP7C
SW3: BOOT; SW_SPST_EVQP7C
SW4: FUNCTION; SW_SPST_EVQP7C
TP1: VBUS; TestPoint_Pad_D1.0mm
TP2: BAT; TestPoint_Pad_D1.0mm
TP3: SYS; TestPoint_Pad_D1.0mm
TP4: 3V3; TestPoint_Pad_D1.0mm
TP5: GND; TestPoint_Pad_D1.0mm
TP6: SCL; TestPoint_Pad_D1.0mm
TP7: SDA; TestPoint_Pad_D1.0mm
TP8: U0TX; TestPoint_Pad_D1.0mm
TP9: U0RX; TestPoint_Pad_D1.0mm
TP10: GNSS_TX; TestPoint_Pad_D1.0mm
TP11: GNSS_RX; TestPoint_Pad_D1.0mm
TP12: GNSS_PPS; TestPoint_Pad_D1.0mm
TP13: GNSS_RST; TestPoint_Pad_D1.0mm
TP14: BQ_INT; TestPoint_Pad_D1.0mm
TP15: TYPEC_INT; TestPoint_Pad_D1.0mm
TP16: GNSS_3V0; TestPoint_Pad_D1.0mm
TP17: ANT_ON; TestPoint_Pad_D1.0mm
U1: ESP32-S3-WROOM-1U-N16R8; ESP32-S3-WROOM-1U_MOTO_REVA
U2: BQ25628ERYKR; BQ25628E_RYK0018A
U3: TPS63070RNMR; TI_RNM0015A_VQFN-15
U4: TUSB320LAIRWBR; Texas_X2QFN-12_1.6x1.6mm_P0.4mm
U5: QMI8658C@0x6B; QMI8658C_LGA-14_2.5x3.0mm
U6: LIS2MDLTR@0x1E; LGA-12_2x2mm_P0.5mm
U7: TPS7A2030PDBVR; SOT-23-5
U8: TXU0202DCUR; VSSOP-8_2.3x2mm_P0.5mm_NoSilk
U9: SN74LVC1G17DBVR; SOT-23-5_NoSilk
U10: LC76GABMD; Quectel_LC76GABMD_LCC18_LGA10
U11: TPD2EUSB30DRTR; Texas_DRT0003A_SON-3_1x1mm_P0.65mm_NoSilk

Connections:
/3V3: C6.1, C16.1, C17.1, C19.1, C20.1, C22.1, C23.1, C24.1, C25.1, C27.1, C29.1, FB1.1, R7.1, R8.1, R9.1, R16.1, R17.1, R21.1, R22.1, R24.1, R26.1, R27.1, R28.1, R29.1, R30.1, R31.1, TP4.1, U1.2 (3V3), U3.7 (VOUT), U3.8 (VOUT), U4.12 (VDD), U5.5 (VDDIO), U5.8 (VDD), U5.10 (RESV), U5.12 (CS), U6.3 (CS), U6.9 (VDD), U6.10 (VDD_IO), U7.1 (IN), U7.3 (EN), U8.3 (VCCA), U8.6 (OE), U9.5 (VCC)
/3V3_DISPLAY: C1.1, C2.1, FB1.2, J3.21 (FPC_21), J3.22 (FPC_22), J3.23 (FPC_23), J3.24 (FPC_24), J3.26 (FPC_26)
/3V3_PG_N: R26.2, U3.2 (PG)
/BAT: C9.1, J2.1 (BAT+), TP2.1, U2.8 (BAT)
/BAT_TS: J2.2 (NTC), R19.2, R20.1, U2.6 (TS)
/BOOT_N: R30.2, SW3.1, U1.27 (IO0)
/BQ_BTST: C7.1, U2.1 (BTST)
/BQ_CE_N: R23.1, U2.14 (CE)
/BQ_ILIM: R18.1, U2.4 (ILIM)
/BQ_PMID: C12.1, U2.17 (PMID)
/BQ_QON: SW1.1, U2.7 (QON)
/BQ_REGN: C8.1, U2.2 (REGN)
/BQ_SW: C7.2, L1.1, U2.16 (SW)
/BQ_TS_BIAS: R19.1, U2.5 (TS_BIAS)
/CHARGER_INT_N: R22.2, TP14.1, U1.33 (IO40), U2.11 (INT)
/CHARGER_PG_N: R17.2, U2.3 (PG)
/CHARGER_STAT_N: R21.2, U2.10 (STAT)
/FUNC_KEY_N: R31.2, SW4.1, U1.18 (IO10)
/GND: C1.2, C2.2, C3.2, C4.2, C5.2, C6.2, C8.2, C9.2, C10.2, C11.2, C12.2, C13.2, C14.2, C15.2, C16.2, C17.2, C18.2, C19.2, C20.2, C21.2, C22.2, C23.2, C24.2, C25.2, C26.2, C27.2, C28.2, C29.2, C30.2, C32.2, C33.2, C34.2, C35.2, C36.2, C37.2, D1.2, D2.2, J1.A1 (GND), J1.A12 (GND), J1.B1 (GND), J1.B12 (GND), J2.3 (BAT-), J3.1 (FPC_1), J3.4 (FPC_4), J3.7 (FPC_7), J3.10 (FPC_10), J3.20 (FPC_20), J3.25 (FPC_25), J3.31 (FPC_31), J4.2 (GND), J4.3 (GND), Q1.2 (S), R12.2, R18.2, R20.2, R23.2, R25.2, R32.2, SW1.2, SW2.2, SW3.2, SW4.2, TP5.1, U1.1 (GND), U1.40 (GND), U1.41 (EP_GND), U2.15 (GND), U3.4 (GND), U3.10 (PGND), U3.15 (VSEL), U4.3 (PORT), U4.5 (ADDR), U4.10 (GND), U4.11 (EN_N), U5.1 (SDO/SA0), U5.6 (GND), U5.7 (GND), U6.6 (GND), U6.8 (GND), U7.2 (GND)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
/GNSS_3V0: C28.1, C30.1, C34.1, C35.1, C36.1, C37.1, TP16.1, U7.5 (OUT), U8.7 (VCCB), U10.6 (V_BCKP), U10.8 (VCC)
/GNSS_ANT_BIASED: C31.1, D2.1, J4.1 (RF), L3.2
/GNSS_ANT_ON: TP17.1, U10.13 (ANT_ON)
/GNSS_PPS_3V0: TP12.1, U9.2 (A), U10.4 (1PPS)
/GNSS_PPS_3V3: U1.34 (IO41), U9.4 (Y)
/GNSS_RESET_DRV: Q1.1 (G), R32.1, U1.24 (IO47)
/GNSS_RESET_N_1V8: Q1.3 (D), TP13.1, U10.9 (RESET_N)
/GNSS_RF_IN: C33.1, R33.2, U10.11 (RF_IN)
/GNSS_RF_MATCH_IN: C31.2, C32.1, R33.1
/GNSS_RX_3V0: TP11.1, U8.8 (B1Y), U10.3 (RXD)
/GNSS_TX_3V0: TP10.1, U8.1 (B2), U10.2 (TXD)
/GNSS_UART_RX_3V3: U1.11 (IO18), U8.4 (A2Y)
/GNSS_UART_TX_3V3: U1.10 (IO17), U8.5 (A1)
/GNSS_VDD_RF: L3.1, U10.14 (VDD_RF)
/I2C_SCL: J3.27 (FPC_27), R27.2, TP6.1, U1.22 (IO14), U2.13 (SCL), U4.8 (SCL/OUT2), U5.13 (SCL), U6.1 (SCL/SPC)
/I2C_SDA: J3.28 (FPC_28), R28.2, TP7.1, U1.8 (IO15), U2.12 (SDA), U4.7 (SDA/OUT1), U5.14 (SDA), U6.4 (SDA/SDI/SDO)
/LCD_CLK: J3.14 (FPC_14), R5.2
/LCD_CLK_MCU: R5.1, U1.31 (IO38)
/LCD_CS_N: J3.17 (FPC_17), R6.2
/LCD_CS_N_MCU: R6.1, U1.20 (IO12)
/LCD_RESET_N: J3.18 (FPC_18), R7.2, U1.39 (IO1)
/LCD_SIO0: J3.16 (FPC_16), R1.2
/LCD_SIO0_MCU: R1.1, U1.4 (IO4)
/LCD_SIO1: J3.15 (FPC_15), R2.2
/LCD_SIO1_MCU: R2.1, U1.5 (IO5)
/LCD_SIO2: J3.12 (FPC_12), R3.2
/LCD_SIO2_MCU: R3.1, U1.6 (IO6)
/LCD_SIO3: J3.13 (FPC_13), R4.2
/LCD_SIO3_MCU: R4.1, U1.7 (IO7)
/LCD_TE: J3.11 (FPC_11), U1.21 (IO13)
/LIS2MDL_C1: C26.1, U6.5 (C1)
/MAG_DRDY: U1.35 (IO42), U6.7 (INT/DRDY)
/MCU_EN: C21.1, R29.2, SW2.1, U1.3 (EN)
/QMI_INT1: U1.23 (IO21), U5.4 (INT1)
/QMI_INT2: U1.32 (IO39), U5.9 (INT2)
/SYS: C10.1, C11.1, C14.1, C15.1, L1.2, R34.1, TP3.1, U2.9 (SYS), U3.12 (VIN), U3.13 (VIN)
/TPS63070_FB: R24.2, R25.1, U3.5 (FB)
/TPS63070_L1: L2.1, U3.11 (L1)
/TPS63070_L2: L2.2, U3.9 (L2)
/TPS63070_VAUX: C18.1, U3.3 (VAUX)
/TPS_EN_SYNC: R34.2, U3.1 (PS/SYNC), U3.14 (EN)
/TP_INT_N: J3.30 (FPC_30), R9.2, U1.19 (IO11)
/TP_RESET_N: J3.29 (FPC_29), R8.2, U1.38 (IO2)
/TYPEC_INT_N: R16.2, TP15.1, U1.25 (IO48), U4.6 (INT_N/OUT3)
/TYPEC_VBUS_DET: R15.2, U4.4 (VBUS_DET)
/UART0_RX: TP9.1, U1.36 (RXD0/IO44)
/UART0_TX: TP8.1, U1.37 (TXD0/IO43)
/USB_CC1: J1.A5 (CC1), U4.1 (CC1)
/USB_CC2: J1.B5 (CC2), U4.2 (CC2)
/USB_D_N_CONN: J1.A7 (D-), J1.B7 (D-), R14.1, U11.3 (D-)
/USB_D_N_MCU: R14.2, U1.13 (USB_D-)
/USB_D_P_CONN: J1.A6 (D+), J1.B6 (D+), R13.1, U11.1 (D+)
/USB_D_P_MCU: R13.2, U1.14 (USB_D+)
/USB_SHIELD: C3.1, J1.S1 (SHIELD), R12.1
/USB_VBUS: C4.1, C5.1, C13.1, D1.1, J1.A4 (VBUS), J1.A9 (VBUS), J1.B4 (VBUS), J1.B9 (VBUS), R15.1, TP1.1, U2.18 (VBUS)

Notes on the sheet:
MOTO GPS REV A — FUNCTIONAL EVT SCHEMATIC
NOT FOR FABRICATION: complete electrical capture; PCB/layout/footprint/power-coupon validation still required
MCU / NATIVE USB / DISPLAY
USB-C / POWER PATH
MOTION + MAGNETOMETER
GNSS / LEVEL SHIFT / RF
BQ25628E ILIM: IINREG = KILIM / RILIM = 2500 A-ohm / 4.99 kohm = 0.501 A typical
TPS63070: SYS -> 100k -> shared EN/PS-SYNC; 1uH + 44uF nominal allowed, effective C/load-step requires coupon
1559-1606 MHz multi-constellation RF path: no GPS-only narrow SAW; pi network starts DNP / 0R / DNP
